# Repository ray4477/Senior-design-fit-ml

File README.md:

# Senior-design-fit-ml
dance wearables

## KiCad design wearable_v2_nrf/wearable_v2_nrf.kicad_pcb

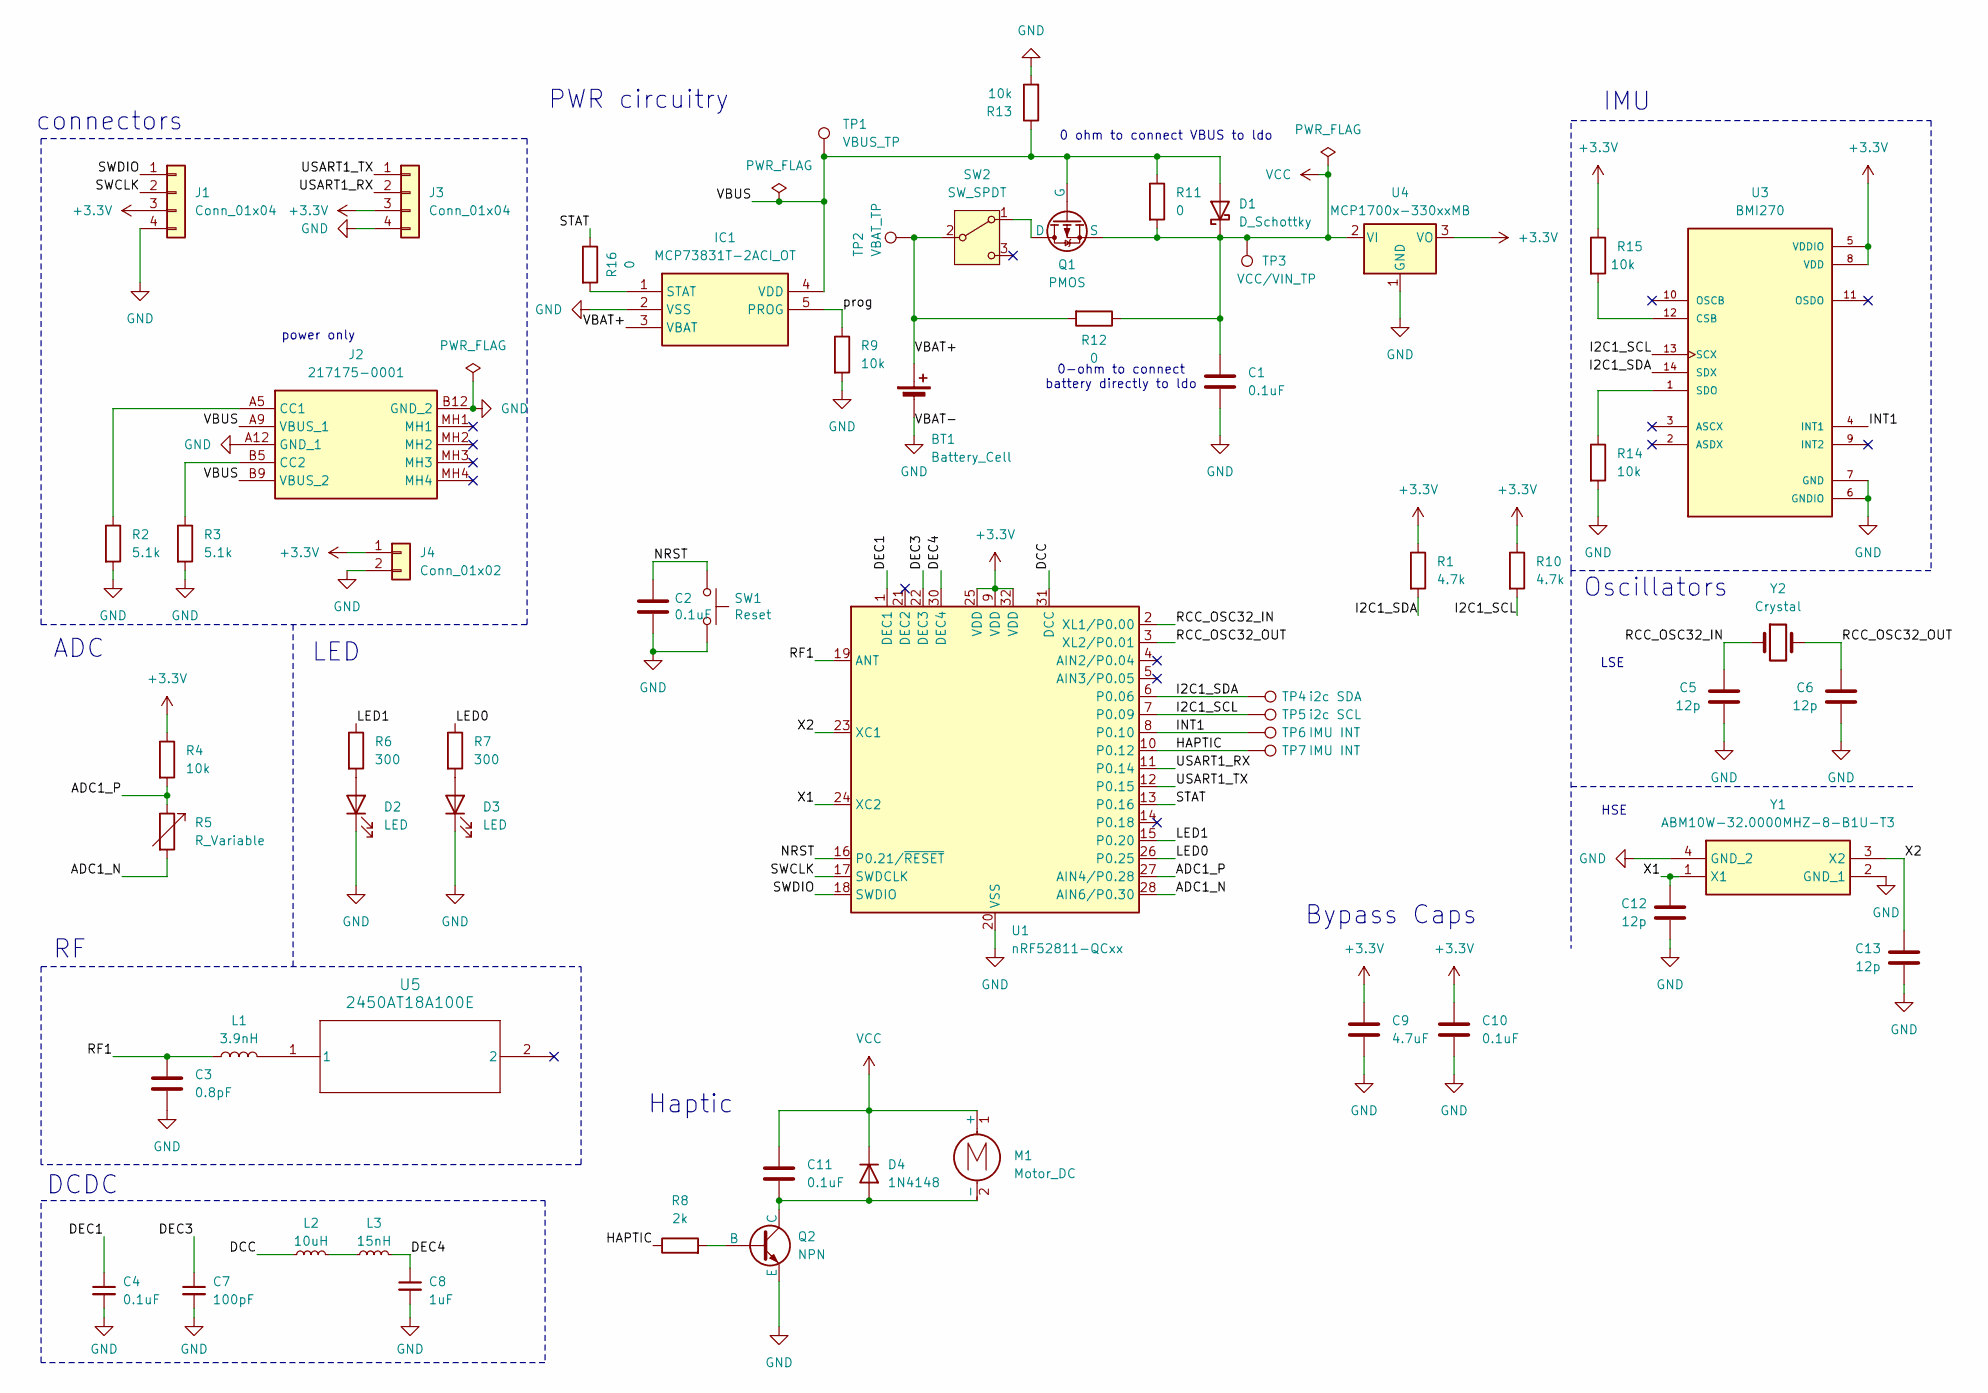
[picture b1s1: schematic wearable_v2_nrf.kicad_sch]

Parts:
BT1: Battery_Cell; Molex_PicoBlade_53047-0210_1x02_P1.25mm_Vertical
C1, C2, C10, C11: 0.1uF; C_0805_2012Metric
C3: 0.8pF; C_0805_2012Metric
C4: 0.1uF; C_0805_2012Metric; Manufacturer_Part_Number KGM05AR71C104KN
C5, C6, C12, C13: 12p; C_0805_2012Metric
C7: 100pF; C_0805_2012Metric; Manufacturer_Part_Number KGM05ACG1H101JN
C8: 1uF; C_0805_2012Metric; Manufacturer_Part_Number CM05X7R105K06AH-HE
C9: 4.7uF; C_0805_2012Metric
D1: D_Schottky; SOD2513X120N
D2, D3: LED; LED_0805_2012Metric
D4: 1N4148; D_SOD-323_HandSoldering
IC1: MCP73831T-2ACI_OT; SOT-23-5; Mouser Part Number 579-MCP73831T-2ACIOT
J1, J3: Conn_01x04; PinHeader_1x04_P2.54mm_Vertical
J2: 217175-0001; 2171750001; Mouser Part Number 538-217175-0001
J4: Conn_01x02; PinHeader_1x02_P2.54mm_Vertical
L1: 3.9nH; L_0805_2012Metric
L2: 10uH; L_0805_2012Metric; Manufacturer_Part_Number KLZ1608MHR100WTD25
L3: 15nH; L_0805_2012Metric; Manufacturer_Part_Number LQG15WZ15NG02D
M1: Motor_DC; PinHeader_1x02_P2.54mm_Vertical
Q1: PMOS; SOT96P240X110-3N
Q2: NPN; SOT95P240X115-3N
R1, R10: 4.7k; R_0805_2012Metric
R2, R3: 5.1k; R_0805_2012Metric
R4, R9, R13, R14, R15: 10k; R_0805_2012Metric
R5: R_Variable; PinHeader_1x02_P2.54mm_Vertical
R6, R7: 300; R_0805_2012Metric
R8: 2k; R_0805_2012Metric
R11, R12, R16: 0; R_0805_2012Metric
SW1: Reset; SW_SPST_B3SL-1002P
SW2: SW_SPDT; PinHeader_1x03_P2.54mm_Vertical
TP1: VBUS_TP; TestPoint_THTPad_1.0x1.0mm_Drill0.5mm
TP2: VBAT_TP; TestPoint_THTPad_1.0x1.0mm_Drill0.5mm
TP3: VCC/VIN_TP; TestPoint_THTPad_1.0x1.0mm_Drill0.5mm
TP4: i2c SDA; TestPoint_THTPad_1.5x1.5mm_Drill0.7mm
TP5: i2c SCL; TestPoint_THTPad_1.5x1.5mm_Drill0.7mm
TP6, TP7: IMU INT; TestPoint_THTPad_1.5x1.5mm_Drill0.7mm
U1: nRF52811-QCxx; QFN-32-1EP_5x5mm_P0.5mm_EP3.6x3.6mm_ThermalVias
U3: BMI270; XDCR_BMI270
U4: MCP1700x-330xxMB; SOT-89-3
U5: 2450AT18A100E; 2450AT18A100E_JOT
Y1: ABM10W-32.0000MHZ-8-B1U-T3; ABM10W240000MHZ8K1ZT3; Mouser Part Number 815-10W32-8B1UT
Y2: Crystal; Crystal_SMD_MicroCrystal_CC8V-T1A-2Pin_2.0x1.2mm

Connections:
+3.3V: C9.1, C10.1, J1.3, J3.3, J4.1, R1.1, R4.1, R10.1, R15.1, U1.9 (VDD), U1.25 (VDD), U1.32 (VDD), U3.5 (VDDIO), U3.8 (VDD), U4.3 (VO)
/ADC1_N: R5.2, U1.28 (AIN6/P0.30)
/ADC1_P: R4.2, R5.1, U1.27 (AIN4/P0.28)
/DCC: L2.1, U1.31 (DCC)
/DEC1: C4.1, U1.1 (DEC1)
/DEC3: C7.1, U1.22 (DEC3)
/DEC4: C8.1, L3.2, U1.30 (DEC4)
/HAPTIC: R8.1, TP7.1, U1.10 (P0.12)
/I2C1_SCL: R10.2, TP5.1, U1.7 (P0.09), U3.13 (SCX)
/I2C1_SDA: R1.2, TP4.1, U1.6 (P0.06), U3.14 (SDX)
/INT1: TP6.1, U1.8 (P0.10), U3.4 (INT1)
/LED0: R7.1, U1.26 (P0.25)
/LED1: R6.1, U1.15 (P0.20)
/NRST: C2.1, SW1.1, U1.16 (P0.21/~RESET)
/RCC_OSC32_IN: C5.2, U1.2 (XL1/P0.00), Y2.1
/RCC_OSC32_OUT: C6.2, U1.3 (XL2/P0.01), Y2.2
/RF1: C3.1, L1.1, U1.19 (ANT)
/STAT: R16.1, U1.13 (P0.16)
/SWCLK: J1.2, U1.17 (SWDCLK)
/SWDIO: J1.1, U1.18 (SWDIO)
/USART1_RX: J3.2, U1.11 (P0.14)
/USART1_TX: J3.1, U1.12 (P0.15)
/VBAT+: BT1.1 (+), IC1.3 (VBAT), R12.2, SW2.2 (B), TP2.1
/VBUS: D1.2 (A), IC1.4 (VDD), J2.A9 (VBUS_1), J2.B9 (VBUS_2), Q1.1 (G), R11.1, R13.1, TP1.1
/X1: C12.2, U1.24 (XC2), Y1.1 (X1)
/X2: C13.2, U1.23 (XC1), Y1.3 (X2)
/prog: IC1.5 (PROG), R9.1
GND: BT1.2 (-), C1.2, C2.2, C3.2, C4.2, C5.1, C6.1, C7.2, C8.2, C9.2, C10.2, C12.1, C13.1, D2.1 (K), D3.1 (K), IC1.2 (VSS), J1.4, J2.A12 (GND_1), J2.B12 (GND_2), J3.4, J4.2, Q2.2 (E), R2.2, R3.2, R9.2, R13.2, R14.2, SW1.2, U1.20 (VSS), U1.29 (VSS), U1.33 (VSS), U3.6 (GNDIO), U3.7 (GND), U4.1 (GND), Y1.2 (GND_1), Y1.4 (GND_2)
unnamed: D2.2 (A), R6.2
unnamed: D3.2 (A), R7.2
unnamed: C11.2, D4.2 (A), M1.2 (-), Q2.3 (C)
unnamed: IC1.1 (STAT), R16.2
unnamed: J2.A5 (CC1), R2.1
unnamed: J2.B5 (CC2), R3.1
unnamed: L1.2, U5.1
unnamed: L2.2, L3.1
unnamed: Q1.3 (D), SW2.1 (A)
unnamed: Q2.1 (B), R8.2
unnamed: R15.2, U3.12 (CSB)
unnamed: R14.1, U3.1 (SDO)
VCC: C1.1, C11.1, D1.1 (K), D4.1 (K), M1.1 (+), Q1.2 (S), R11.2, R12.1, TP3.1, U4.2 (VI)

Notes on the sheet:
0 ohm to connect VBUS to ldo
power only
PWR circuitry
IMU
Bypass Caps
LSE
LED
ADC
DCDC
connectors
HSE
0-ohm to connect battery directly to ldo
Oscillators
Haptic

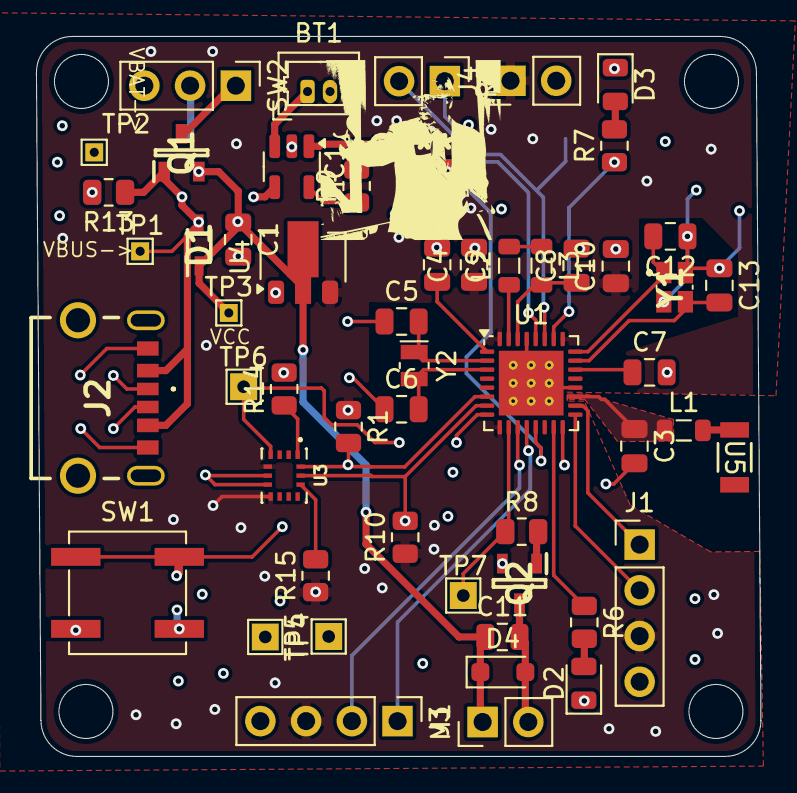
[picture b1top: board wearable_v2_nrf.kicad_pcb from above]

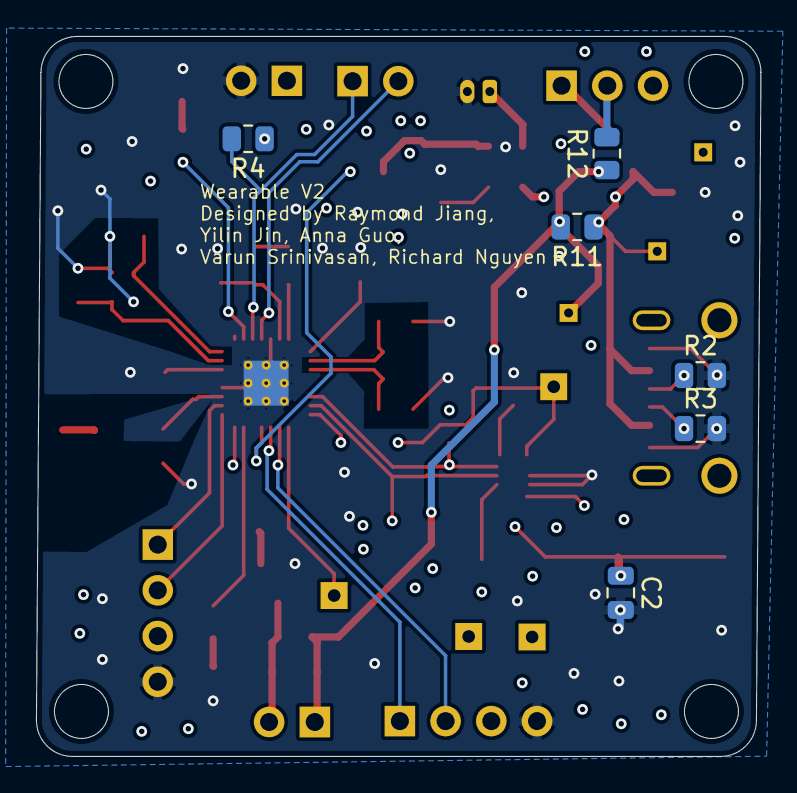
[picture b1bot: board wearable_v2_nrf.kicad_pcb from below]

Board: 4 copper layers, 40.2 x 40.0 mm, 60 parts (6 on the bottom side), 41 nets.

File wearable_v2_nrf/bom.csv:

Reference,Value,Datasheet,Footprint,Qty,mouser #,DNP,Mouser link
BT1,Battery_Cell,~,Connector_JST:JST_PH_B2B-PH-K_1x02_P2.00mm_Vertical,1,306-B2BPHKSLFSNPP,,https://www.mouser.com/ProductDetail/Molex/217175-0001?qs=DR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
"C1,C2,C4,C10,C11",0.1uF,~,Capacitor_SMD:C_0805_2012Metric,5,581-KAF21KR72A104KL,,
C3,0.8pF,~,Capacitor_SMD:C_0805_2012Metric,1,581-600F0R8BT,,https://www.mouser.com/ProductDetail/KYOCERA-AVX/600F0R8BT25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
"C5,C6,C12,C13",12p,~,Capacitor_SMD:C_0805_2012Metric,4,581-08055A120CAT2A,,
C7,100pF,~,Capacitor_SMD:C_0805_2012Metric,1,80-C0805C101KCRTU,,
C8,1uF,~,Capacitor_SMD:C_0805_2012Metric,1,187-CL21B105KAFNNNG,,
C9,4.7uF,~,Capacitor_SMD:C_0805_2012Metric,1,,,
D1,D_Schottky,~,A_wearables:SOD2513X120N,1,,,
"D2,D3",LED,~,LED_SMD:LED_0805_2012Metric,2,,,
D4,1N4148,https://assets.nexperia.com/documents/data-sheet/1N4148_1N4448.pdf,Diode_SMD:D_SOD-323_HandSoldering,1,,,
IC1,MCP73831T-2ACI_OT,http://ww1.microchip.com/downloads/en/DeviceDoc/20001984g.pdf,Package_TO_SOT_SMD:SOT-23-5,1,,,
J1,Conn_01x04,~,Connector_PinHeader_2.54mm:PinHeader_1x04_P2.54mm_Vertical,1,,,
J2,217175-0001,https://www.molex.com/pdm_docs/sd/2171750001_sd.pdf,A_wearables:2171750001,1,,,
J3,Conn_01x03,~,Connector_PinHeader_2.54mm:PinHeader_1x03_P2.54mm_Vertical,1,,,
L1,3.9nH,~,Inductor_SMD:L_0805_2012Metric,1,,,
L2,10uH,~,Inductor_SMD:L_0805_2012Metric,1,,,
L3,15nH,~,Inductor_SMD:L_0805_2012Metric,1,,,
M1,Motor_DC,~,Connector_PinHeader_2.54mm:PinHeader_1x02_P2.54mm_Vertical,1,,,
Q1,PMOS,https://ngspice.sourceforge.io/docs/ngspice-html-manual/manu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,A_wearables:SOT96P240X110-3N,1,,,
Q2,NPN,https://www.mouser.com/ProductDetail/Comchip-Technology/SS80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,A_wearables:SOT95P240X115-3N,1,,,
"R1,R10",4.7k,~,Resistor_SMD:R_0805_2012Metric,2,,,
"R2,R3",5.1k,~,Resistor_SMD:R_0805_2012Metric,2,,,
"R4,R9",10k,~,Resistor_SMD:R_0805_2012Metric,2,,,
R5,R_Variable,~,Connector_PinSocket_2.54mm:PinSocket_1x02_P2.54mm_Horizontal,1,,,
"R6,R7",300,~,Resistor_SMD:R_0805_2012Metric,2,,,
R8,2k,~,Resistor_SMD:R_0805_2012Metric,1,,,
SW1,Reset,,Button_Switch_SMD:SW_SPST_B3SL-1002P,1,,,
TP1,VBUS_TP,~,TestPoint:TestPoint_THTPad_1.0x1.0mm_Drill0.5mm,1,,,
TP2,VBAT_TP,~,TestPoint:TestPoint_THTPad_1.0x1.0mm_Drill0.5mm,1,,,
TP3,VCC/VIN_TP,~,TestPoint:TestPoint_THTPad_1.0x1.0mm_Drill0.5mm,1,,,
TP4,i2c SDA,~,TestPoint:TestPoint_THTPad_1.5x1.5mm_Drill0.7mm,1,,,
TP5,i2c SCL,~,TestPoint:TestPoint_THTPad_1.5x1.5mm_Drill0.7mm,1,,,
"TP6,TP7",IMU INT,~,TestPoint:TestPoint_THTPad_1.5x1.5mm_Drill0.7mm,2,,,
U1,nRF52811-QCxx,https://infocenter.nordicsemi.com/pdf/nRF52811_PS_v1.0.pdf,Package_DFN_QFN:QFN-32-1EP_5x5mm_P0.5mm_EP3.6x3.6mm_ThermalVias,1,,,
U3,BMI270,,A_wearables:XDCR_BMI270,1,,,
U4,MCP1700x-330xxMB,http://ww1.microchip.com/downloads/en/DeviceDoc/20001826D.pdf,Package_TO_SOT_SMD:SOT-89-3,1,,,
U5,2450AT18A100E,2450AT18A100E,A_wearables:2450AT18A100E_JOT,1,,,
Y1,ABM10W-32.0000MHZ-8-B1U-T3,https://componentsearchengine.com/Datasheets/1/ABM10W-32.000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,A_wearables:ABM10W240000MHZ8K1ZT3,1,,,
Y2,Crystal,~,Crystal:Crystal_SMD_MicroCrystal_CC8V-T1A-2Pin_2.0x1.2mm,1,,,

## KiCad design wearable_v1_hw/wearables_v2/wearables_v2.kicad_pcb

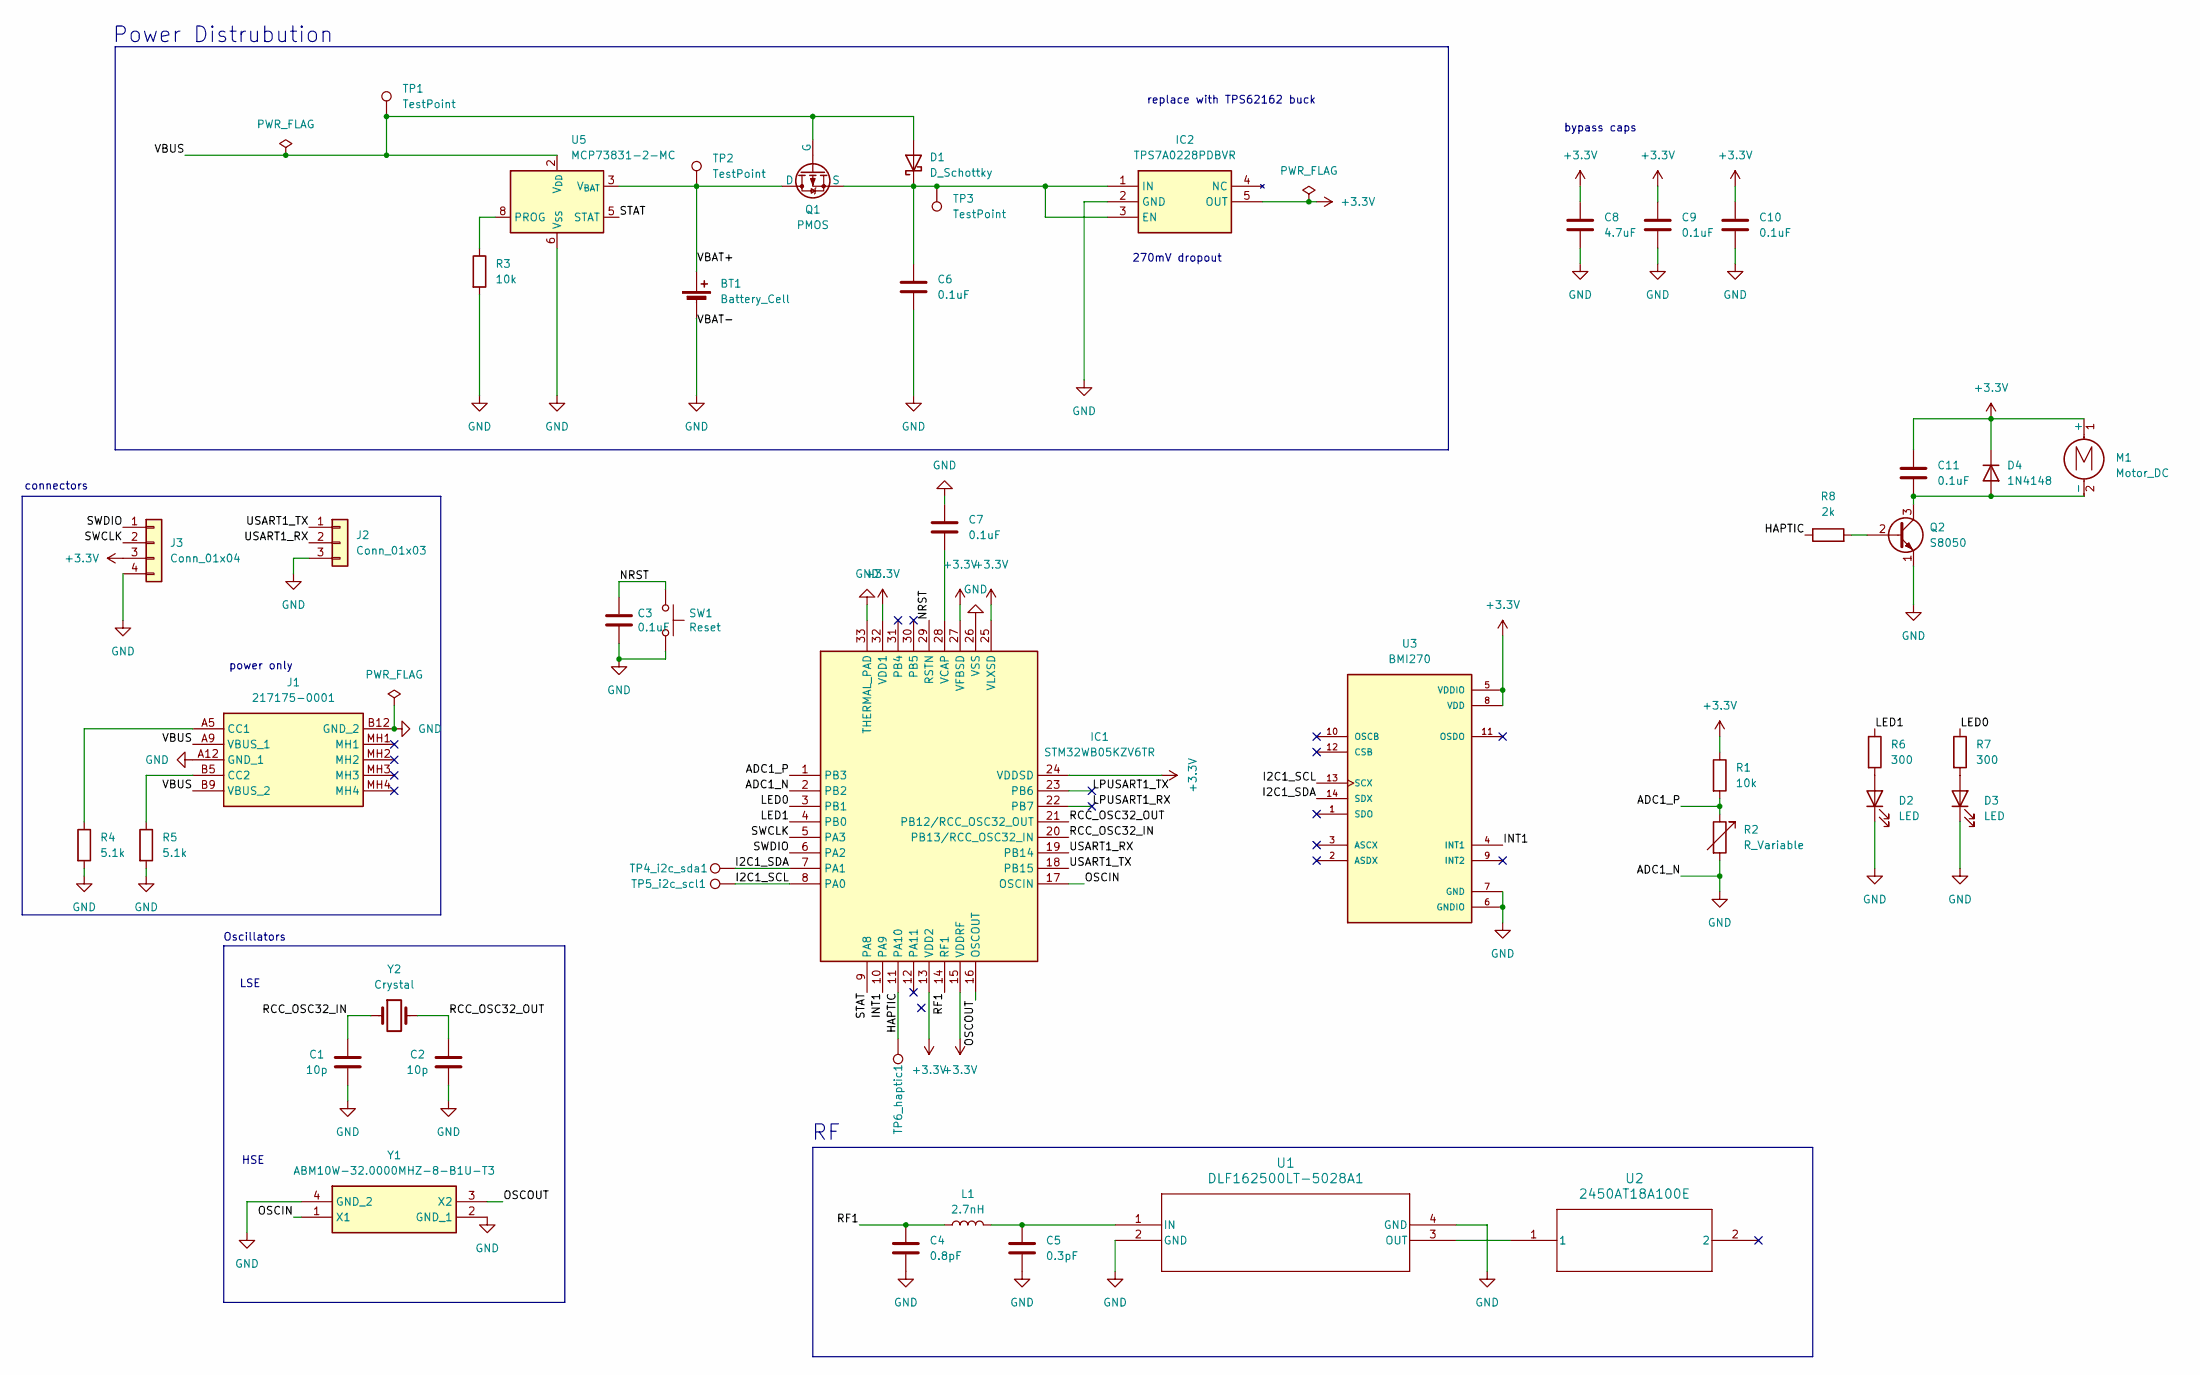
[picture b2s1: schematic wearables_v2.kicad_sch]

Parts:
BT1: Battery_Cell; JST_PH_B2B-PH-K_1x02_P2.00mm_Vertical
C1, C2: 10p; C_0805_2012Metric
C3, C6, C7, C9, C10, C11: 0.1uF; C_0805_2012Metric
C4: 0.8pF; C_0805_2012Metric
C5: 0.3pF; C_0805_2012Metric
C8: 4.7uF; C_0805_2012Metric
D1: D_Schottky; SOD2513X120N
D2, D3: LED; LED_0805_2012Metric
D4: 1N4148; D_DO-35_SOD27_P7.62mm_Horizontal
IC1: STM32WB05KZV6TR; QFN50P500X500X100-33N-D; Mouser Part Number 511-STM32WB05KNV6TR
IC2: TPS7A0228PDBVR; SOT95P280X145-5N; Mouser Part Number 595-TPS7A0228PDBVR
J1: 217175-0001; 2171750001; Mouser Part Number 538-217175-0001
J2: Conn_01x03; PinHeader_1x03_P2.54mm_Vertical
J3: Conn_01x04; PinHeader_1x04_P2.54mm_Vertical
L1: 2.7nH; L_0805_2012Metric
M1: Motor_DC; PinHeader_1x02_P2.54mm_Vertical
Q1: PMOS; SOT96P240X110-3N
Q2: S8050; TO-92_Inline
R1, R3: 10k; R_0805_2012Metric
R2: R_Variable; PinSocket_1x02_P2.54mm_Horizontal
R4, R5: 5.1k; R_0805_2012Metric
R6, R7: 300; R_0805_2012Metric
R8: 2k; R_0805_2012Metric
SW1: Reset; SW_SPST_B3SL-1002P
TP1, TP2, TP3: TestPoint; TestPoint_THTPad_1.0x1.0mm_Drill0.5mm
TP4_i2c_sda1, TP5_i2c_scl1, TP6_haptic1: TestPoint; 5000
U1: DLF162500LT-5028A1; DLF-4_1P6X0P8
U2: 2450AT18A100E; 2450AT18A100E_JOT
U3: BMI270; XDCR_BMI270
U5: MCP73831-2-MC; DFN-8-1EP_3x2mm_P0.5mm_EP1.7x1.4mm
Y1: ABM10W-32.0000MHZ-8-B1U-T3; ABM10W240000MHZ8K1ZT3; Mouser Part Number 815-10W32-8B1UT
Y2: Crystal; Crystal_SMD_MicroCrystal_CC8V-T1A-2Pin_2.0x1.2mm

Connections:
+3.3V: C8.1, C9.1, C10.1, C11.1, D4.1 (K), IC1.13 (VDD2), IC1.15 (VDDRF), IC1.24 (VDDSD), IC1.25 (VLXSD), IC1.27 (VFBSD), IC1.32 (VDD1), IC2.5 (OUT), J3.3, M1.1 (+), R1.1, U3.5 (VDDIO), U3.8 (VDD)
/ADC1_P: IC1.1 (PB3), R1.2, R2.1
/HAPTIC: IC1.11 (PA10), R8.1, TP6_haptic1.1
/I2C1_SCL: IC1.8 (PA0), TP5_i2c_scl1.1, U3.13 (SCX)
/I2C1_SDA: IC1.7 (PA1), TP4_i2c_sda1.1, U3.14 (SDX)
/INT1: IC1.10 (PA9), U3.4 (INT1)
/LED0: IC1.3 (PB1), R7.1
/LED1: IC1.4 (PB0), R6.1
/LPUSART1_RX: IC1.22 (PB7)
/LPUSART1_TX: IC1.23 (PB6)
/NRST: C3.1, IC1.29 (RSTN), SW1.1
/OSCIN: IC1.17 (OSCIN), Y1.1 (X1)
/OSCOUT: IC1.16 (OSCOUT), Y1.3 (X2)
/RCC_OSC32_IN: C1.2, IC1.20 (PB13/RCC_OSC32_IN), Y2.1
/RCC_OSC32_OUT: C2.2, IC1.21 (PB12/RCC_OSC32_OUT), Y2.2
/RF1: C4.1, IC1.14 (RF1), L1.1
/STAT: IC1.9 (PA8), U5.5 (STAT)
/SWCLK: IC1.5 (PA3), J3.2
/SWDIO: IC1.6 (PA2), J3.1
/USART1_RX: IC1.19 (PB14), J2.2
/USART1_TX: IC1.18 (PB15), J2.1
/VBAT+: BT1.1 (+), Q1.1 (D), TP2.1, U5.3 (V_{BAT}), U5.4 (V_{BAT})
/VBUS: D1.2 (A), J1.A9 (VBUS_1), J1.B9 (VBUS_2), Q1.2 (G), TP1.1, U5.1 (V_{DD}), U5.2 (V_{DD})
GND: BT1.2 (-), C1.1, C2.1, C3.2, C4.2, C5.2, C6.2, C7.1, C8.2, C9.2, C10.2, D2.1 (K), D3.1 (K), IC1.2 (PB2), IC1.26 (VSS), IC1.33 (THERMAL_PAD), IC2.2 (GND), J1.A12 (GND_1), J1.B12 (GND_2), J2.3, J3.4, Q2.1 (E), R2.2, R3.2, R4.2, R5.2, SW1.2, U1.2 (GND), U1.4 (GND), U3.6 (GNDIO), U3.7 (GND), U5.6 (V_{SS}), Y1.2 (GND_1), Y1.4 (GND_2); also elsewhere on the board
unnamed 24: C6.1, D1.1 (K), IC2.1 (IN), IC2.3 (EN), Q1.3 (S), TP3.1; also elsewhere on the board
unnamed: D2.2 (A), R6.2
unnamed: D3.2 (A), R7.2
unnamed: C11.2, D4.2 (A), M1.2 (-), Q2.3 (C)
unnamed: C7.2, IC1.28 (VCAP)
unnamed: J1.A5 (CC1), R4.1
unnamed: J1.B5 (CC2), R5.1
unnamed: Q2.2 (B), R8.2
unnamed: C5.1, L1.2, U1.1 (IN)
unnamed: U1.3 (OUT), U2.1
unnamed: R3.1, U5.8 (PROG)

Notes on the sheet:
270mV dropout
HSE
Oscillators
replace with TPS62162 buck
connectors
LSE
Power Distrubution
bypass caps
power only

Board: 2 copper layers, 47 parts (0 on the bottom side), 33 nets, no tracks yet.

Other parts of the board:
SW2: SW_Nidec_CAS-120A1; Nidec_Copal_CAS-120A

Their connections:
GND: SW2.3 (A); also elsewhere on the board
unnamed 24: SW2.1 (C); also elsewhere on the board

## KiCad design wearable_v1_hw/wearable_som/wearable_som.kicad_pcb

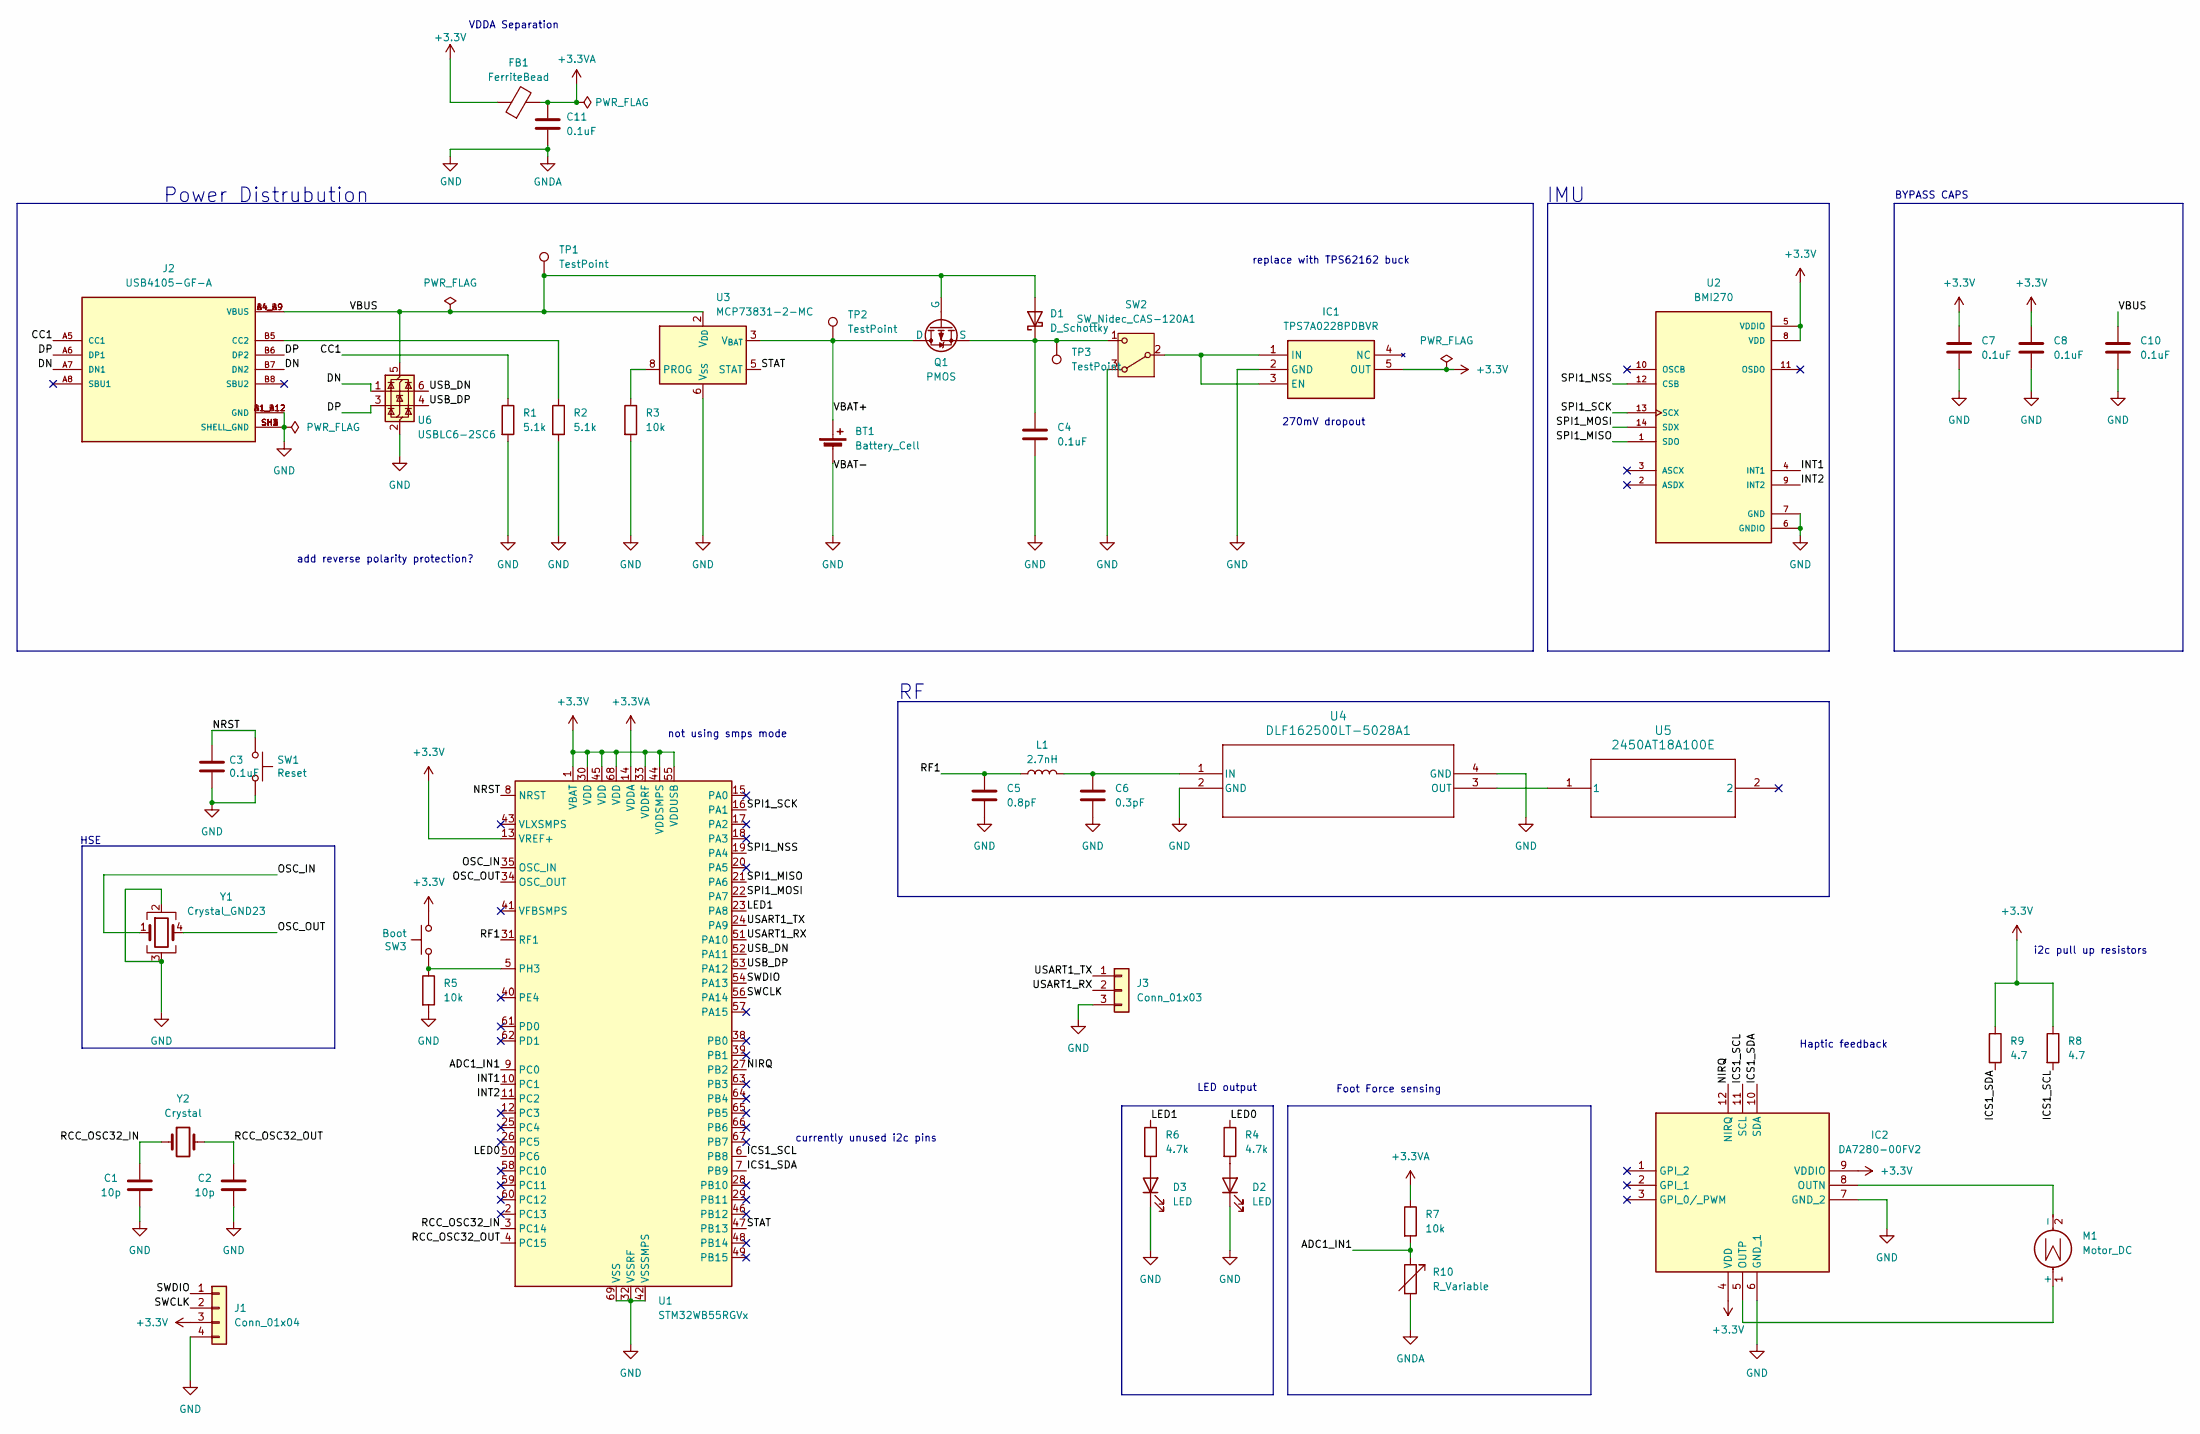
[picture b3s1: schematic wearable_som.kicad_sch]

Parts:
BT1: Battery_Cell; JST_PH_B2B-PH-K_1x02_P2.00mm_Vertical
C1, C2: 10p; C_0805_2012Metric
C3, C4, C7, C8, C10: 0.1uF; C_0805_2012Metric
C5: 0.8pF; C_0805_2012Metric
C6: 0.3pF; C_0805_2012Metric
C11: 0.1uF; C_0805_2012Metric; Mouser Part Number 80-C0805C104M5R
D1: D_Schottky; SOD2513X120N
D2, D3: LED; LED_0805_2012Metric
FB1: FerriteBead; L_0805_2012Metric; Mouser Part Number 704-MFBW1V2012-121-R
IC1: TPS7A0228PDBVR; SOT95P280X145-5N; Mouser Part Number 595-TPS7A0228PDBVR
IC2: DA7280-00FV2; QFN65P300X300X84-12N; Manufacturer_Part_Number DA7280-00FV2
J1: Conn_01x04; PinHeader_1x04_P2.54mm_Vertical
J2: USB4105-GF-A; GCT_USB4105-GF-A; PARTREV B4
J3: Conn_01x03; PinHeader_1x03_P2.54mm_Vertical
L1: 2.7nH; L_0805_2012Metric
M1: Motor_DC; TestPoint_2Pads_Pitch5.08mm_Drill1.3mm
Q1: PMOS; SOT96P240X110-3N
R1, R2: 5.1k; R_0805_2012Metric
R3, R5, R7: 10k; R_0805_2012Metric
R4, R6: 4.7k; R_0805_2012Metric
R8, R9: 4.7; R_0805_2012Metric
R10: R_Variable; PinSocket_1x02_P2.54mm_Horizontal
SW1: Reset; SW_SPST_B3SL-1002P
SW2: SW_Nidec_CAS-120A1; Nidec_Copal_CAS-120A
SW3: Boot; SW_SPST_B3SL-1002P
TP1, TP2, TP3: TestPoint; TestPoint_THTPad_1.0x1.0mm_Drill0.5mm
U1: STM32WB55RGVx; QFN-68-1EP_8x8mm_P0.4mm_EP6.4x6.4mm
U2: BMI270; XDCR_BMI270
U3: MCP73831-2-MC; DFN-8-1EP_3x2mm_P0.5mm_EP1.7x1.4mm
U4: DLF162500LT-5028A1; DLF-4_1P6X0P8
U5: 2450AT18A100E; 2450AT18A100E_JOT
U6: USBLC6-2SC6; SOT-23-6
Y1: Crystal_GND23; Crystal_SMD_2016-4Pin_2.0x1.6mm
Y2: Crystal; Crystal_SMD_MicroCrystal_CC8V-T1A-2Pin_2.0x1.2mm

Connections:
+3.3V: C7.1, C8.1, FB1.1, IC1.5 (OUT), IC2.4 (VDD), IC2.9 (VDDIO), J1.3, R8.1, R9.1, SW3.2, U1.1 (VBAT), U1.13 (VREF+), U1.30 (VDD), U1.33 (VDDRF), U1.44 (VDDSMPS), U1.45 (VDD), U1.55 (VDDUSB), U1.68 (VDD), U2.5 (VDDIO), U2.8 (VDD); also elsewhere on the board
+3.3VA: C11.1, FB1.2, R7.1, U1.14 (VDDA)
/ADC1_IN1: R7.2, R10.1, U1.9 (PC0)
/CC1: J2.A5 (CC1), R1.1
/DN: J2.A7 (DN1), J2.B7 (DN2), U6.1 (I/O1)
/DP: J2.A6 (DP1), J2.B6 (DP2), U6.3 (I/O2)
/ICS1_SCL: IC2.11 (SCL), R8.2, U1.6 (PB8)
/ICS1_SDA: IC2.10 (SDA), R9.2, U1.7 (PB9)
/INT1: U1.10 (PC1), U2.4 (INT1)
/INT2: U1.11 (PC2), U2.9 (INT2)
/LED0: R4.1, U1.50 (PC6)
/LED1: R6.1, U1.23 (PA8)
/NIRQ: IC2.12 (NIRQ), U1.27 (PB2)
/NRST: C3.1, SW1.1, U1.8 (NRST)
/OSC_IN: U1.35 (OSC_IN), Y1.1
/OSC_OUT: U1.34 (OSC_OUT), Y1.4
/RCC_OSC32_IN: C1.2, U1.3 (PC14), Y2.1
/RCC_OSC32_OUT: C2.2, U1.4 (PC15), Y2.2
/RF1: C5.1, L1.1, U1.31 (RF1)
/SPI1_MISO: U1.21 (PA6), U2.1 (SDO)
/SPI1_MOSI: U1.22 (PA7), U2.14 (SDX)
/SPI1_NSS: U1.19 (PA4), U2.12 (CSB)
/SPI1_SCK: U1.16 (PA1), U2.13 (SCX)
/STAT: U1.47 (PB13), U3.5 (STAT)
/SWCLK: J1.2, U1.56 (PA14)
/SWDIO: J1.1, U1.54 (PA13)
/USART1_RX: J3.2, U1.51 (PA10)
/USART1_TX: J3.1, U1.24 (PA9)
/USB_DN: U1.52 (PA11), U6.6 (I/O1)
/USB_DP: U1.53 (PA12), U6.4 (I/O2)
/VBAT+: BT1.1 (+), Q1.1 (D), TP2.1, U3.3 (V_{BAT}), U3.4 (V_{BAT})
/VBUS: C10.1, D1.2 (A), J2.A4_B9 (VBUS), J2.B4_A9 (VBUS), Q1.2 (G), TP1.1, U3.1 (V_{DD}), U3.2 (V_{DD}), U6.5 (VBUS)
GND: BT1.2 (-), C1.1, C2.1, C3.2, C4.2, C5.2, C6.2, C7.2, C8.2, C10.2, C11.2, D2.1 (K), D3.1 (K), IC1.2 (GND), IC2.6 (GND_1), IC2.7 (GND_2), J1.4, J2.A1_B12 (GND), J2.B1_A12 (GND), J2.SH1 (SHELL_GND), J2.SH2 (SHELL_GND), J2.SH3 (SHELL_GND), J2.SH4 (SHELL_GND), J3.3, R1.2, R2.2, R3.2, R5.2, R10.2, SW1.2, SW2.3 (A), U1.32 (VSSRF), U1.42 (VSSSMPS), U1.69 (VSS), U2.6 (GNDIO), U2.7 (GND), U3.6 (V_{SS}), U4.2 (GND), U4.4 (GND), U6.2 (GND), Y1.2, Y1.3; also elsewhere on the board
unnamed: C4.1, D1.1 (K), Q1.3 (S), SW2.1 (C), TP3.1
unnamed: D2.2 (A), R4.2
unnamed: D3.2 (A), R6.2
unnamed: IC1.1 (IN), IC1.3 (EN), SW2.2 (B)
unnamed: IC2.8 (OUTN), M1.2 (-)
unnamed: IC2.5 (OUTP), M1.1 (+)
unnamed: J2.B5 (CC2), R2.1
unnamed: R5.1, SW3.1, U1.5 (PH3)
unnamed: R3.1, U3.8 (PROG)
unnamed: C6.1, L1.2, U4.1 (IN)
unnamed: U4.3 (OUT), U5.1

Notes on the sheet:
replace with TPS62162 buck
IMU
VDDA Separation
HSE
LED output
i2c pull up resistors
not using smps mode
Haptic feedback
Power Distrubution
BYPASS CAPS
currently unused i2c pins
270mV dropout
Foot Force sensing
add reverse polarity protection?

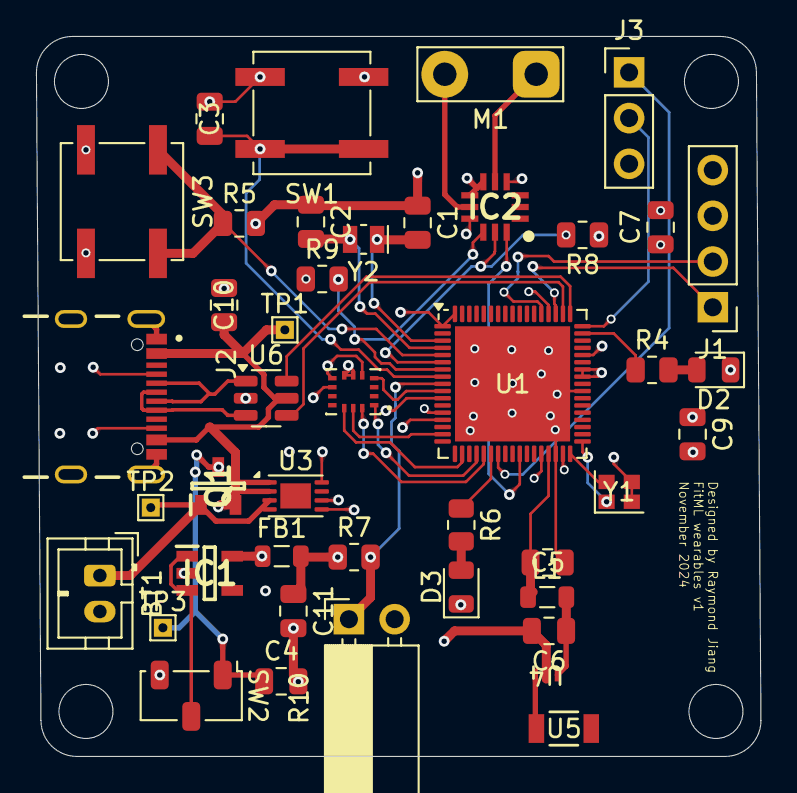
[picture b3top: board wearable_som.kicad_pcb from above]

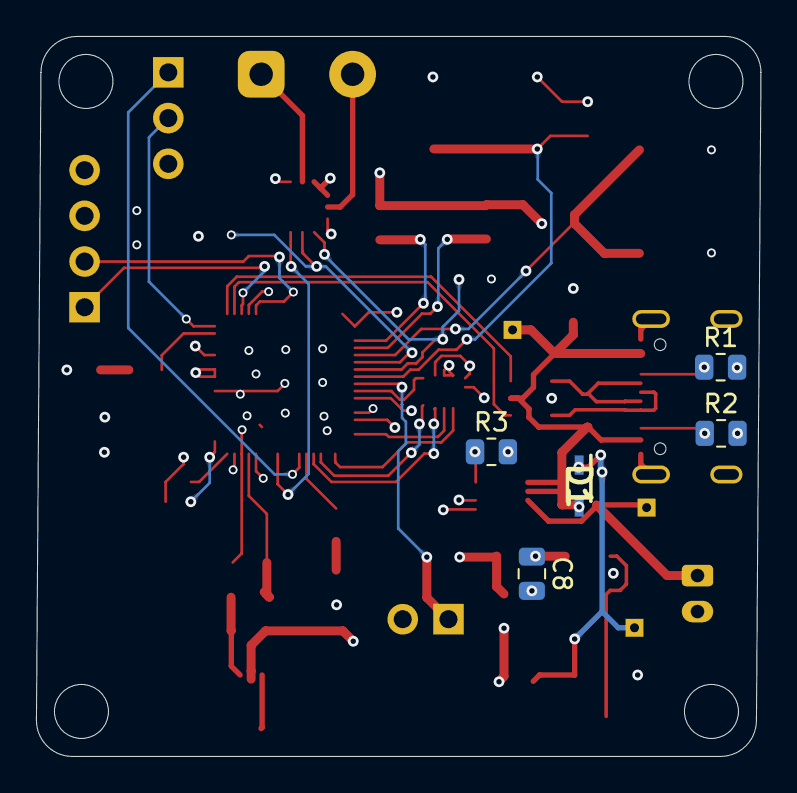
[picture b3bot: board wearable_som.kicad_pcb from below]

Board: 4 copper layers, 40.2 x 40.0 mm, 48 parts (5 on the bottom side), 44 nets.

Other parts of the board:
C9: 0.1uF; C_0805_2012Metric

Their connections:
+3.3V: C9.1; also elsewhere on the board
GND: C9.2; also elsewhere on the board

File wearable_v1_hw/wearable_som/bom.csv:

Reference,Value,Datasheet,Footprint,Qty,DNP,mouser order
BT1,Battery_Cell,~,Connector_JST:JST_PH_B2B-PH-K_1x02_P2.00mm_Vertical,1,,10
"C1,C2",10p,~,Capacitor_SMD:C_0805_2012Metric,2,,20
"C3,C4,C7,C8,C10,C11",0.1uF,~,Capacitor_SMD:C_0805_2012Metric,6,,60
C5,0.8pF,~,Capacitor_SMD:C_0805_2012Metric,1,,10
C6,0.3pF,~,Capacitor_SMD:C_0805_2012Metric,1,,10
D1,D_Schottky,~,wearable_som_footprint_lib:SOD2513X120N,1,,10
"D2,D3",LED,~,LED_SMD:LED_0805_2012Metric,2,,20
FB1,FerriteBead,~,Inductor_SMD:L_0805_2012Metric,1,,10
IC1,TPS7A0228PDBVR,https://www.ti.com/lit/gpn/TPS7A02,wearable_som_footprint_lib:SOT95P280X145-5N,1,,10
IC2,DA7280-00FV2,https://www.renesas.com/us/en/products/interface-connectivit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,wearable_som_footprint_lib:QFN65P300X300X84-12N,1,,10
J1,Conn_01x04,~,Connector_PinHeader_2.54mm:PinHeader_1x04_P2.54mm_Vertical,1,,10
J2,USB4105-GF-A,,wearable_som_footprint_lib:GCT_USB4105-GF-A,1,,10
J3,Conn_01x03,~,Connector_PinHeader_2.54mm:PinHeader_1x03_P2.54mm_Vertical,1,,10
L1,2.7nH,~,Inductor_SMD:L_0805_2012Metric,1,,10
M1,Motor_DC,~,TestPoint:TestPoint_2Pads_Pitch5.08mm_Drill1.3mm,1,,10
Q1,PMOS,https://ngspice.sourceforge.io/docs/ngspice-html-manual/manu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,wearable_som_footprint_lib:SOT96P240X110-3N,1,,10
"R1,R2",5.1k,~,Resistor_SMD:R_0805_2012Metric,2,,20
"R3,R5,R7",10k,~,Resistor_SMD:R_0805_2012Metric,3,,30
"R4,R6",4.7k,~,Resistor_SMD:R_0805_2012Metric,2,,20
"R8,R9",4.7,~,Resistor_SMD:R_0805_2012Metric,2,,20
R10,R_Variable,~,Connector_PinSocket_2.54mm:PinSocket_1x02_P2.54mm_Horizontal,1,,10
SW1,Reset,,Button_Switch_SMD:SW_SPST_B3SL-1002P,1,,10
SW2,SW_Nidec_CAS-120A1,https://www.nidec-components.com/e/catalog/switch/cas.pdf,Button_Switch_SMD:Nidec_Copal_CAS-120A,1,,10
SW3,Boot,,Button_Switch_SMD:SW_SPST_B3SL-1002P,1,,10
"TP1,TP2,TP3",TestPoint,~,TestPoint:TestPoint_THTPad_1.0x1.0mm_Drill0.5mm,3,,30
U1,STM32WB55RGVx,https://www.st.com/resource/en/datasheet/stm32wb55rg.pdf,Package_DFN_QFN:QFN-68-1EP_8x8mm_P0.4mm_EP6.4x6.4mm,1,,10
U2,BMI270,,wearable_som_footprint_lib:XDCR_BMI270,1,,10
U3,MCP73831-2-MC,http://ww1.microchip.com/downloads/en/DeviceDoc/20001984g.pdf,Package_DFN_QFN:DFN-8-1EP_3x2mm_P0.5mm_EP1.7x1.4mm,1,,10
U4,DLF162500LT-5028A1,DLF162500LT-5028A1,wearable_som_footprint_lib:DLF-4_1P6X0P8,1,,10
U5,2450AT18A100E,2450AT18A100E,wearable_som_footprint_lib:2450AT18A100E_JOT,1,,10
U6,USBLC6-2SC6,https://www.st.com/resource/en/datasheet/usblc6-2.pdf,Package_TO_SOT_SMD:SOT-23-6,1,,10
Y1,Crystal_GND23,~,Crystal:Crystal_SMD_2016-4Pin_2.0x1.6mm,1,,10
Y2,Crystal,~,Crystal:Crystal_SMD_MicroCrystal_CC8V-T1A-2Pin_2.0x1.2mm,1,,10

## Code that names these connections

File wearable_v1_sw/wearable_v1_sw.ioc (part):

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Mcu.Name=STM32WB55RGVx
Mcu.Package=VFQFPN68
Mcu.UserName=STM32WB55RGVx
PA1.Mode=Full_Duplex_Master
PA1.Signal=SPI1_SCK
PA10.Mode=Asynchronous
PA10.Signal=USART1_RX
PA11.Mode=Device
PA11.Signal=USB_DM
PA12.Mode=Device
PA12.Signal=USB_DP
PA13.Mode=Serial_Wire
PA13.Signal=SYS_JTMS-SWDIO
PA14.Mode=Serial_Wire
PA14.Signal=SYS_JTCK-SWCLK
PA4.Mode=NSS_Signal_Hard_Output
PA4.Signal=SPI1_NSS
PA5.Signal=GPIO_Output
PA6.Mode=Full_Duplex_Master
PA6.Signal=SPI1_MISO
PA7.Mode=Full_Duplex_Master
PA7.Signal=SPI1_MOSI
PA8.Signal=GPIO_Output
PA9.Mode=Asynchronous
PA9.Signal=USART1_TX
PB0.Signal=GPIO_Output
PB1.Signal=GPIO_Output
PB10.Mode=I2C
PB10.Signal=I2C3_SCL
PB11.Mode=I2C
PB11.Signal=I2C3_SDA
PB13.Signal=GPIO_Input
PB8.Mode=I2C
PB8.Signal=I2C1_SCL
PB9.Mode=I2C
PB9.Signal=I2C1_SDA
PC0.Signal=ADCx_IN1
PC1.Signal=GPIO_Input
PC14-OSC32_IN.Mode=LSE-External-Oscillator
PC14-OSC32_IN.Signal=RCC_OSC32_IN
PC15-OSC32_OUT.Mode=LSE-External-Oscillator
PC15-OSC32_OUT.Signal=RCC_OSC32_OUT
PC2.Signal=GPIO_Input
RCC.HSE_VALUE=32000000
RCC.SYSCLKFreq_VALUE=64000000
RCC.SYSCLKSource=RCC_SYSCLKSOURCE_PLLCLK
board=custom

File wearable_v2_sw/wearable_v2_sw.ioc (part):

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Mcu.Name=STM32WB05KZVx
Mcu.Package=VFQFPN32
Mcu.UserName=STM32WB05KZVx
PA0.Mode=I2C
PA0.Signal=I2C1_SCL
PA1.Mode=I2C
PA1.Signal=I2C1_SDA
PA2.Mode=Serial_Wire
PA2.Signal=DEBUG_SWDIO
PA3.Mode=Serial_Wire
PA3.Signal=DEBUG_SWCLK
PB12.Mode=LSE-External-Oscillator
PB12.Signal=RCC_OSC32_OUT
PB13.Mode=LSE-External-Oscillator
PB13.Signal=RCC_OSC32_IN
PB14.Mode=Asynchronous
PB14.Signal=USART1_RX
PB15.Mode=Asynchronous
PB15.Signal=USART1_TX
PB2.Mode=VIN0_Diff
PB2.Signal=ADC1_VINM0
PB3.Mode=VIN0_Diff
PB3.Signal=ADC1_VINP0
PB6.Mode=Asynchronous
PB6.Signal=LPUART1_TX
PB7.Mode=Asynchronous
PB7.Signal=LPUART1_RX
RCC.HSE_VALUE=32000000
board=custom

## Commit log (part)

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2024-11-08 ioc, schematic started
2024-11-09 done with power circuitry
    uses mcp73831 and ldo for lipo charging
    (^._.^)ﾉ😜
2024-11-10 added imu, rf circuitry📡😹
    💃
2024-11-11 💃added d-,d+ protection, swd, todo statements
    💃
2024-11-11 stuff🤓
2024-11-18 add haptic feedback
2024-11-18 janky app demo
2024-11-20 pcb layout almost done
2024-11-20 init layout done
2024-11-21 layout done v1 - needs rework
2024-11-23 revisions revisions
    2->4 layers
    improved ground plane + ic placement
    added adc for force sensor
2024-11-24 fix drc errors
2024-11-25 final v1 layout done
2025-01-29 wearables v2
2025-02-10 new nrf variant
2025-03-02 Add firmware for nrf
2025-03-02 add fw
2025-03-02 Update ble_imu_wearable
2025-03-02 refactor
2025-03-03 finished nrf schematic/layout 👷‍♂️
2025-03-03 forgot to push schematic
2025-03-17 changes
    fixed mosfet symbol-footprint,
    connection jst->molex pico,
    made HSC closer
2025-03-31 v2 revisions for nrf pcb
    fix imu, fix adc
    includes new firmware for nrf52811
2025-03-31 final nrf board edits + ble sniffer py script
2025-04-01 final pcb design :)
2025-04-03 firmware refactor
2025-04-03 remove dir
2025-04-17 Create fitml_dataproc
2025-04-21 new enclosure, wip
